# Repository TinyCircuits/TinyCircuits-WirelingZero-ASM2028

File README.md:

# TinyCircuits-WirelingZero-ASM2028
# ASM2028 Rev2

The design files are located under design_files/ for the TinyCircuits ASM2028 Rev2 PCB. This is a processor board designed for low-cost Wireling projects. Includes 4 separately addressable Wireling ports.

Format is in Cadsoft Eagle format - Eagle version 6.2 was used for the original design.

For more infomation, check out the product page at TinyCircuits.com

# License:

Design by TinyCircuits.
All design files are released under the Creative Commons Attribution Share-Alike 3.0 License, see the following link for details: http://creativecommons.org/licenses/by-sa/3.0

All text above must be included in any redistribution or derived design

This project uses designs and concepts developed as part of the Arduino project and the LilyPad project.  The TinyCircuits design files themselves (schematics, PCB and libraries) are not directly derived from these works' design files and have been created new, however the concepts and basic architecture behind the TinyDuino and TinyLily products are derived and we thank the hard work of the organizations below for their contributions to open-source hardware:
  
Original Arduino Uno Design by Team Arduino

LilyPad Arduino Design by Leah Buechley and Sparkfun Electronics

Please support the open-source hardware community

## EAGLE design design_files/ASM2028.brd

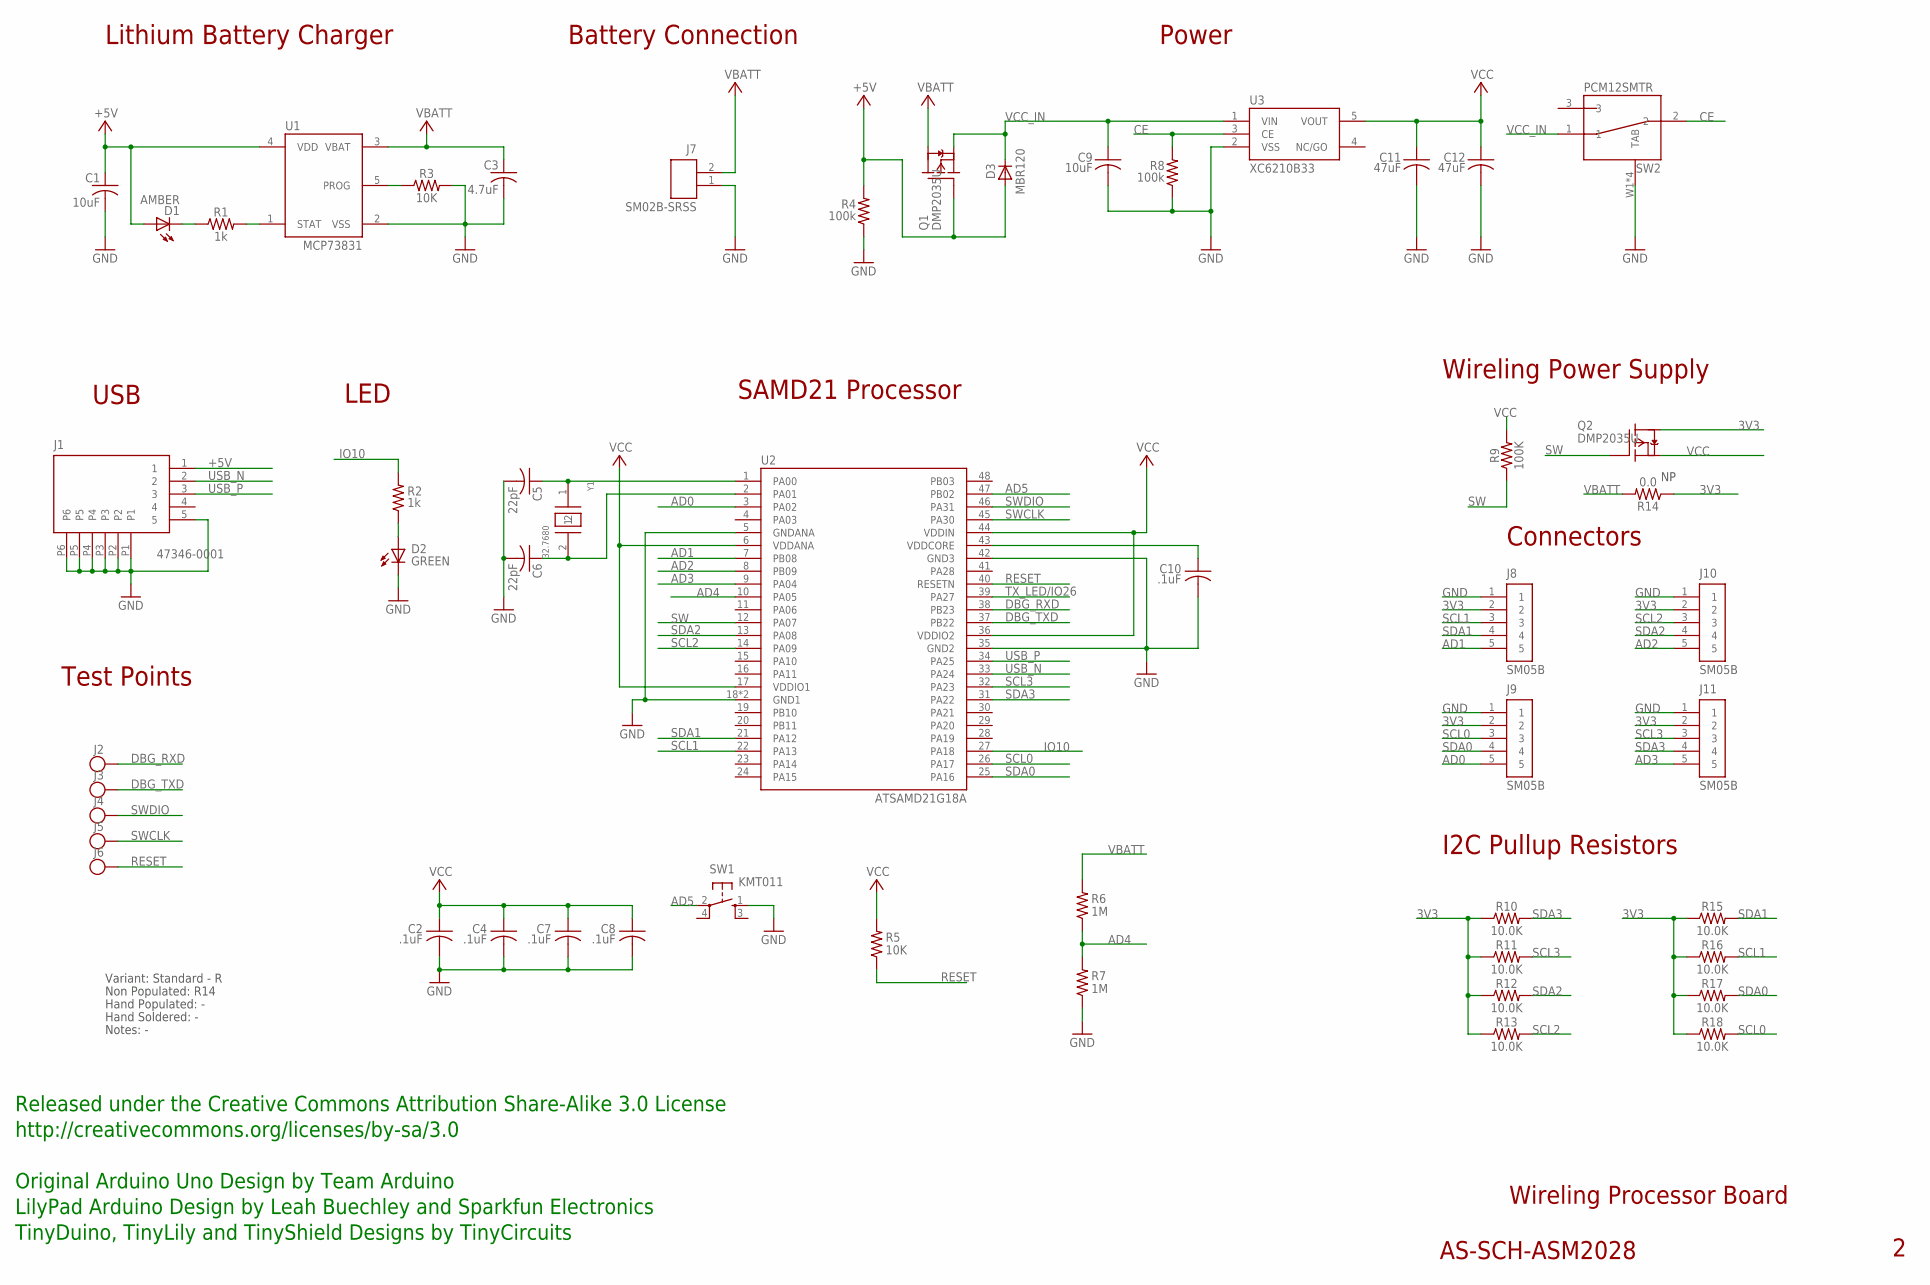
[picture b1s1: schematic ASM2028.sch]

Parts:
C1, C9: 10uF; C0603; PARTNO AS-ITM-00002
C2, C4, C7, C8, C10: .1uF; C0402; PARTNO AS-ITM-00008
C3: 4.7uF; C0603; PARTNO AS-ITM-00088
C5, C6: 22pF; C0402; PARTNO AS-ITM-00211
C11, C12: 47uF; C0603; PARTNO AS-ITM-00558
D1: AMBER; 0402_LED; PARTNO AS-ITM-00058
D2: GREEN; 0402_LED; PARTNO AS-ITM-00038
D3: MBR120; SOD-123FL
J1: 47346-0001; MICRO_USB
J2, J3, J4, J5, J6: TEST_POINT; TEST_POINT_1MM
J7: SM02B-SRSS; JST_SH_2X1
J8, J9, J10, J11: SM05B; JST_SH_5X1_EDGE
Q1: DMP2035U; SOT23A
Q2: DMP2035U; SOT23A; PARTNO AS-ITM-00024
R1, R2: 1k; 0402; PARTNO AS-ITM-00003
R3: 10K; 0402
R4, R8: 100k; 0402; PARTNO AS-ITM-00004
R5: 10K; 0402; PARTNO AS-ITM-00032
R6, R7: 1M; 0402; PARTNO AS-ITM-00005
R9: 100K; 0402
R10, R11, R12, R13, R15, R16, R17, R18: 10.0K; 0402
R14: 0.0; 0402; PARTNO AS-ITM-00076
SW1: KMT011
SW2: PCM12SMTR
U1: MCP73831; SOT-23
U2: ATSAMD21G18A; QFN48; PARTNO AS-ITM-00273
U3: XC6210B33; SOT-25
Y1: 32.7680; ABS06; PARTNO AS-ITM-00279

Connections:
3V3: J8.2, J9.2, J10.2, J11.2, Q2.C (D), R10.1, R11.1, R12.1, R13.1, R14.1, R15.1, R16.1, R17.1, R18.1
+5V: C1.1, D1.1 (A), D3.A, J1.1, Q1.B (G), R4.2, U1.4 (VDD)
AD0: J9.5, U2.3 (PA02)
AD1: J8.5, U2.7 (PB08)
AD2: J10.5, U2.8 (PB09)
AD3: J11.5, U2.9 (PA04)
AD4: R6.1, R7.2, U2.10 (PA05)
AD5: SW1.2, U2.47 (PB02)
CE: R8.2, SW2.2, U3.3 (CE)
DBG_RXD: J2.P$1, U2.38 (PB23)
DBG_TXD: J3.P$1, U2.37 (PB22)
GND: C1.2, C2.2, C3.2, C4.2, C5.2, C6.2, C7.2, C8.2, C9.2, C10.2, C11.2, C12.2, D2.2 (C), J1.5, J1.P1, J1.P2, J1.P3, J1.P4, J1.P5, J1.P6, J7.1 (2), J8.1, J9.1, J10.1, J11.1, R3.2, R4.1, R7.1, R8.1, SW1.1, SW2.W1 (TAB), SW2.W2 (TAB), SW2.W3 (TAB), SW2.W4 (TAB), U1.2 (VSS), U2.5 (GNDANA), U2.18 (GND1), U2.35 (GND2), U2.42 (GND3), U2.EXP (GND1), U3.2 (VSS)
IO10: R2.2, U2.27 (PA18)
unnamed: C5.1, U2.1 (PA00), Y1.1
unnamed: C6.1, U2.2 (PA01), Y1.2
unnamed: D2.1 (A), R2.1
unnamed: D1.2 (C), R1.1
unnamed: R3.1, U1.5 (PROG)
unnamed: R1.2, U1.1 (STAT)
unnamed: C10.1, U2.43 (VDDCORE)
RESET: J6.P$1, R5.1, U2.40 (RESETN)
SCL0: J9.3, R18.2, U2.26 (PA17)
SCL1: J8.3, R16.2, U2.22 (PA13)
SCL2: J10.3, R13.2, U2.14 (PA09)
SCL3: J11.3, R11.2, U2.32 (PA23)
SDA0: J9.4, R17.2, U2.25 (PA16)
SDA1: J8.4, R15.2, U2.21 (PA12)
SDA2: J10.4, R12.2, U2.13 (PA08)
SDA3: J11.4, R10.2, U2.31 (PA22)
SW: Q2.B (G), R9.1, U2.12 (PA07)
SWCLK: J5.P$1, U2.45 (PA30)
SWDIO: J4.P$1, U2.46 (PA31)
TX_LED/IO26: U2.39 (PA27)
USB_N: J1.2, U2.33 (PA24)
USB_P: J1.3, U2.34 (PA25)
VBATT: C3.1, J7.2 (1), Q1.C (D), R6.2, R14.2, U1.3 (VBAT)
VCC: C2.1, C4.1, C7.1, C8.1, C11.1, C12.1, Q2.E (S), R5.2, R9.2, U2.6 (VDDANA), U2.17 (VDDIO1), U2.36 (VDDIO2), U2.44 (VDDIN), U3.5 (VOUT)
VCC_IN: C9.1, D3.C, Q1.E (S), SW2.1, U3.1 (VIN)

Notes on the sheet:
SAMD21 Processor
Power
LED
Wireling Processor Board
AS-SCH-ASM2028
Released under the Creative Commons Attribution Share-Alike 3.0 License
http://creativecommons.org/licenses/by-sa/3.0
Original Arduino Uno Design by Team Arduino
TinyDuino, TinyLily and TinyShield Designs by TinyCircuits
LilyPad Arduino Design by Leah Buechley and Sparkfun Electronics
Lithium Battery Charger
Battery Connection
USB
Test Points
Non Populated: R14
Hand Populated: -
Hand Soldered: -
Notes: -
Variant: Standard - R
Wireling Power Supply
Connectors
I2C Pullup Resistors

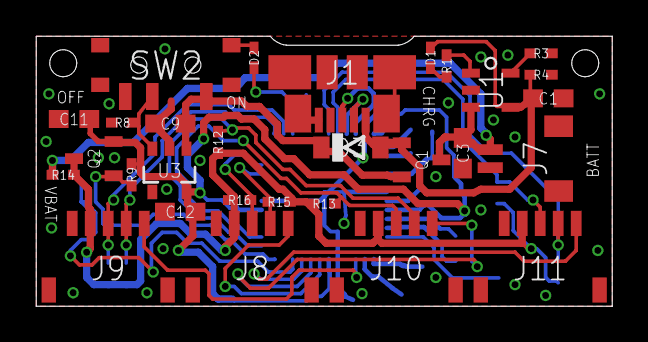
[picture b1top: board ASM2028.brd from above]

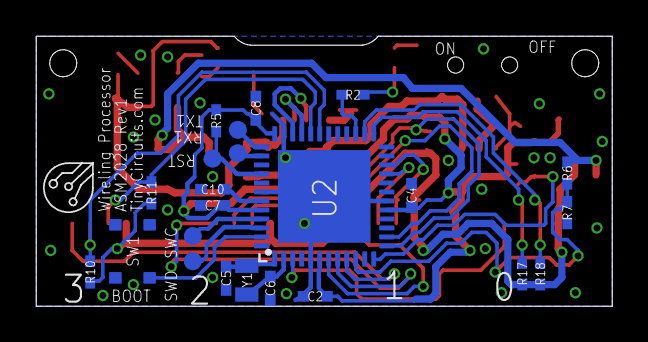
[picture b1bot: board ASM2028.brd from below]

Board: 2 copper layers, 32.0 x 15.0 mm, 53 parts (23 on the bottom side), 37 nets.

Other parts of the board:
U$1: DOCFIELD-TINYCIRCUITS-PCB

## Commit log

2019-12-10 init
2020-03-06 updated product photo to have transparancy
2020-03-06 updated image
2020-06-26 Add CAD data
2020-06-29 Rename files, add dxf, and use new 2D drawing template
2020-07-01 Remove vias in models & drawings, add compact dimension image, and remove a file to reduce size
2020-07-01 Fix typo in drawing
2020-07-01 Fix typo in file name
2020-07-02 Add zip of all CAD files
2020-08-18 Update CAD drawings
